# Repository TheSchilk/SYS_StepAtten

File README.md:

# SYS StepAtten

### Philipp Schilk

A 127 Step Relay Step-Attenuator and 4-way input switcher designed to fit into a [Schiit SYS](https://www.schiit.com/products/sys) enclosure.

## Specifications

| **Spec**                 | **Value**                                 |
|--------------------------|-------------------------------------------|
| Inputs                   | 2x Stereo 3.5mm, 2x Stereo RCA            |
| Attenuator Type          | Constant input impedance                  |
| Expected Input Impedance | 10K (can be adjusted)                     |
| Steps                    | 127 + Relay Mute                          |
| Power Input              | 9Vdc, center positive barrel jack. 500mA+ |
| Power Consumption        | Max 2.25W (250mA at 9VDc)                 |
| Control                  | Internal controls or wired remote control |

## Grounding
All inputs are fully isolated from each other.
RCA grounds can be kept seperate or joined. (Internal Jumper)
Audio ground can be kept seperate or joined to digital ground (Internal Jumper)

## Remote Control
Remote Control connector pinout (looking at connector from back of unit):

| 3V    | GND  |
|-------|------|
| **Sense** | **Poti** |

A remote consists of a potentiometer between 3V and GND with wiper connected to 'Poti'
A 10K resistor has to be placed between GND and Sense for the remote to be detected.
If the remote features a switch, it should short Sense to GND.

## Riser Board
Design files for the 3.5mm Connector Riser board [can be found here](https://github.com/TheSchilk/3.5mm_RiserPCB/releases/tag/v0.1).

## Switch Selection

The SYS is normally fitted with a toggle switch (ALPS SPUN191400), but
a momentary version of that switch also exists (ALPS SPUN190900).

The momentary switch is probably the better choice, but just in case
one wants to harvest as many parts as possible from an original SYS,
both are supported by the firmware.

The internal Jumper CFG1 is used to indicate which kind is installed.

|           *Switch*          | *CFG1 Setting* |
|:---------------------------:|:--------------:|
| Momentary (ALPS SPUN190900) |        0       |
|   Toggle (ALPS SPUN191400)  |        1       |

Note that the unit has to be turned off and on again for this setting 
to take effect.

## Schematics, Gerbers, BOMs, ...
See [Github Releases](https://github.com/TheSchilk/SYS_StepAtten/releases).

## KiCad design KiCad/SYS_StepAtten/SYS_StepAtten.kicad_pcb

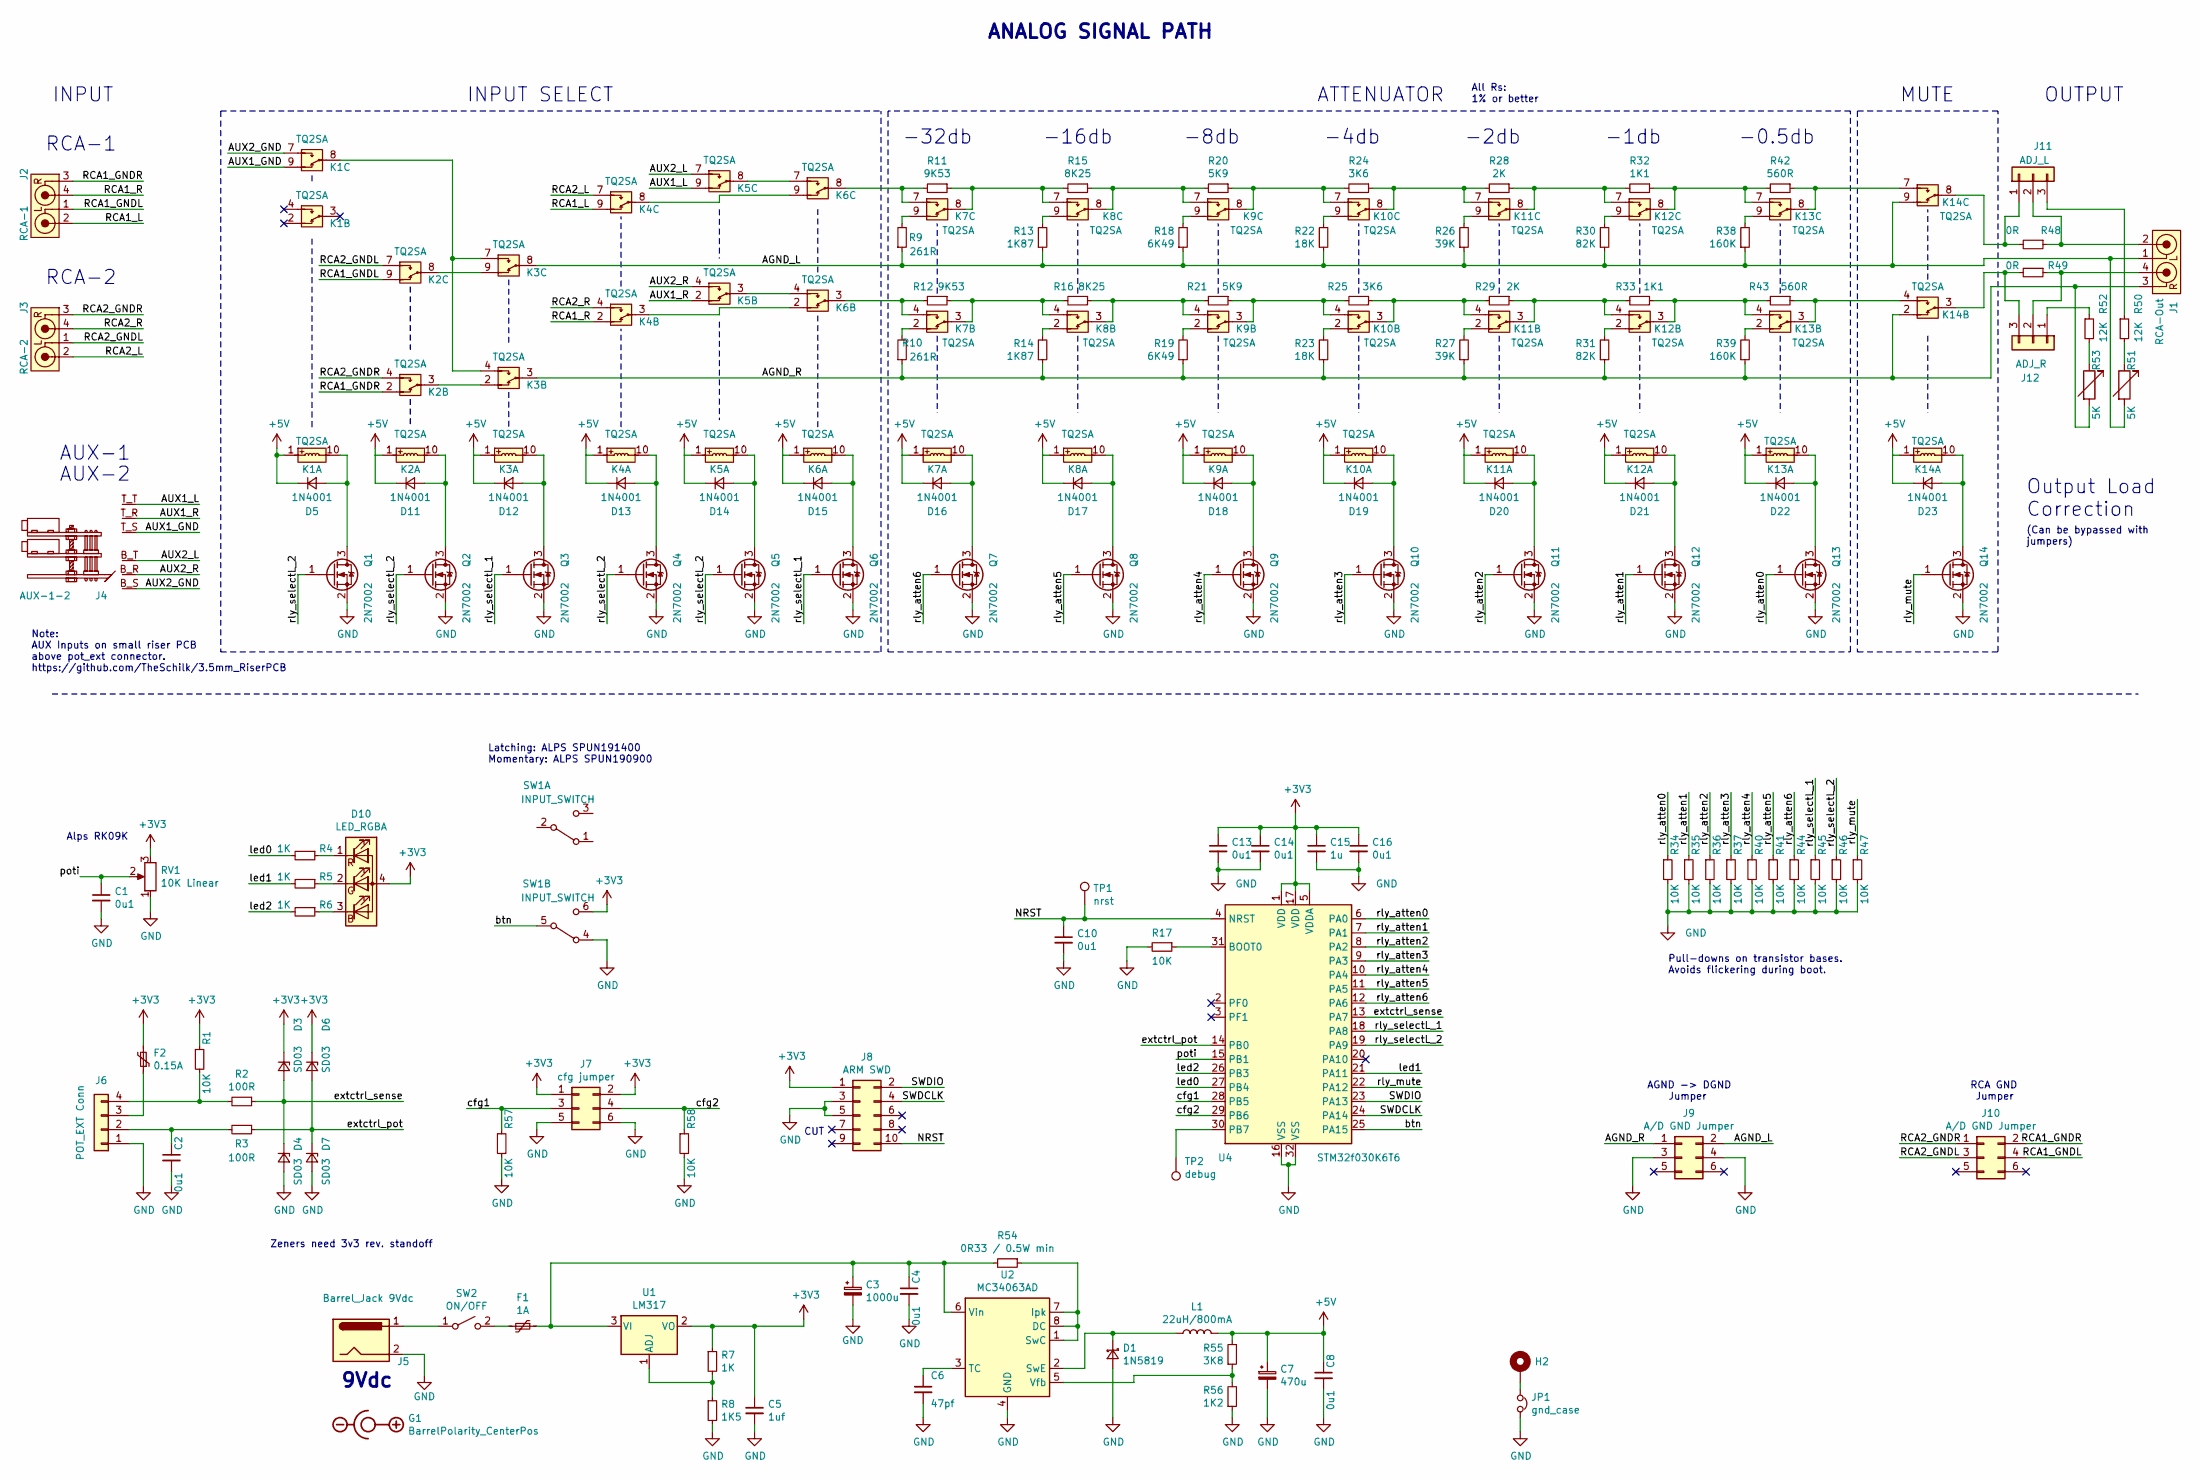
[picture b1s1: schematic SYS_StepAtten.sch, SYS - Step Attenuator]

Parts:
C1, C2, C4, C8, C10, C13, C14, C16: 0u1; C_0603_1608Metric
C3: 1000u; CP_Elec_10x10.5
C5: 1uf; C_0603_1608Metric
C6: 47pf; C_0603_1608Metric
C7: 470u; CP_Elec_8x10.5
C15: 1u; C_0603_1608Metric
D1: 1N5819; D_SOD-123F
D3, D4, D6, D7: SD03; D_SOD-323
D5, D11, D12, D13, D14, D15, D16, D17, D18, D19, D20, D21, D22, D23: 1N4001; D_SOD-123F
D10: LED_RGBA; RGB_LED_1.6x1.6x0.6
F1: 1A; Fuse_1206_3216Metric
F2: 0.15A; Fuse_1206_3216Metric
G1: BarrelPolarity_CenterPos; BarrelPolarity_3mm_CenterPos
H2: MH 1; MountingHole_4.3mm_M4_Pad_Via
J1: RCA-Out; RCA_KobiCon_161-4220-E
J2: RCA-1; RCA_KobiCon_161-4220-E
J3: RCA-2; RCA_KobiCon_161-4220-E
J4: AUX-1-2; 3.5mm_RiserPCB
J5: Barrel_Jack 9Vdc; BarrelJack_Horizontal
J6: POT_EXT Conn; PinHeader_2x02_P2.54mm_Horizontal
J7: cfg jumper; PinHeader_2x03_P2.54mm_Vertical
J8: ARM SWD; PinHeader_2x05_P1.27mm_Vertical_SMD
J9, J10: A/D GND Jumper; PinHeader_2x03_P2.54mm_Vertical
J11: ADJ_L; PinHeader_1x03_P2.54mm_Vertical
J12: ADJ_R; PinHeader_1x03_P2.54mm_Vertical
JP1: gnd_case; R_0603_1608Metric
K1, K2, K3, K4, K5, K6, K7, K8, K9, K10, K11, K12, K13, K14: TQ2SA; Panasonic_TQ2SA
L1: 22uH/800mA; L_Taiyo-Yuden_MD-4040
Q1, Q2, Q3, Q4, Q5, Q6, Q7, Q8, Q9, Q10, Q11, Q12, Q13, Q14: 2N7002; SOT-23
R1, R17, R34, R35, R36, R37, R40, R41, R44, R45, R46, R47, R57, R58: 10K; R_0603_1608Metric
R2, R3: 100R; R_0603_1608Metric
R4, R5, R6, R7: 1K; R_0603_1608Metric
R8: 1K5; R_0603_1608Metric
R9, R10: 261R; R_0603_1608Metric
R11, R12: 9K53; R_0603_1608Metric
R13, R14: 1K87; R_0603_1608Metric
R15, R16: 8K25; R_0603_1608Metric
R18, R19: 6K49; R_0603_1608Metric
R20, R21: 5K9; R_0603_1608Metric
R22, R23: 18K; R_0603_1608Metric
R24, R25: 3K6; R_0603_1608Metric
R26, R27: 39K; R_0603_1608Metric
R28, R29: 2K; R_0603_1608Metric
R30, R31: 82K; R_0603_1608Metric
R32, R33: 1K1; R_0603_1608Metric
R38, R39: 160K; R_0603_1608Metric
R42, R43: 560R; R_0603_1608Metric
R48, R49: 0R; R_0603_1608Metric
R50, R52: 12K; R_0603_1608Metric
R51, R53: 5K; Potentiometer_Bourns_3296W_Vertical
R54: 0R33 / 0.5W min; R_1210_3225Metric
R55: 3K8; R_0603_1608Metric
R56: 1K2; R_0603_1608Metric
RV1: 10K Linear; Potentiometer_Alps_RK09K_Single_Horizontal
SW1: INPUT_SWITCH; ALPS_SPUN191400
SW2: ON/OFF; PinHeader_1x02_P2.54mm_Vertical
TP1: nrst; TestPoint_Pad_2.5x2.5mm
TP2: debug; TestPoint_Pad_2.5x2.5mm
U1: LM317; TO-252-2
U2: MC34063AD; SOIC-8_3.9x4.9mm_P1.27mm
U4: STM32f030K6T6; LQFP-32_7x7mm_P0.8mm

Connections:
+3V3: C5.1, C13.1, C14.1, C15.1, C16.1, D3.1 (K), D6.1 (K), D10.4 (A), F2.2, J7.1, J7.2, J8.1, R1.1, R7.1, RV1.3, SW1.6 (C), U1.2 (VO), U4.1 (VDD), U4.5 (VDDA), U4.17 (VDD)
+5V: C7.1, C8.1, D5.1 (K), D11.1 (K), D12.1 (K), D13.1 (K), D14.1 (K), D15.1 (K), D16.1 (K), D17.1 (K), D18.1 (K), D19.1 (K), D20.1 (K), D21.1 (K), D22.1 (K), D23.1 (K), K1.1, K2.1, K3.1, K4.1, K5.1, K6.1, K7.1, K8.1, K9.1, K10.1, K11.1, K12.1, K13.1, K14.1, L1.2, R55.2
/AGND_L: J1.1, J9.2, K3.8, K14.9, R9.1, R13.1, R18.1, R22.1, R26.1, R30.1, R38.1, R51.2
/AGND_R: J1.3, J9.1, K3.3, K14.2, R10.1, R14.1, R19.1, R23.1, R27.1, R31.1, R39.1, R53.2
/AUX1_GND: J4.T_S, K1.9
/AUX1_L: J4.T_T, K5.9
/AUX1_R: J4.T_R, K5.2
/AUX2_GND: J4.B_S, K1.7
/AUX2_L: J4.B_T, K5.7
/AUX2_R: J4.B_R, K5.4
/NRST: C10.1, J8.10, TP1.1, U4.4 (NRST)
/RCA1_GNDL: J2.1, J10.4, K2.9
/RCA1_GNDR: J2.3, J10.2, K2.2
/RCA1_L: J2.2, K4.9
/RCA1_R: J2.4, K4.2
/RCA2_GNDL: J3.1, J10.3, K2.7
/RCA2_GNDR: J3.3, J10.1, K2.4
/RCA2_L: J3.2, K4.7
/RCA2_R: J3.4, K4.4
/SWDCLK: J8.4, U4.24 (PA14)
/SWDIO: J8.2, U4.23 (PA13)
/btn: SW1.5 (B), U4.25 (PA15)
/cfg1: J7.3, R57.1, U4.28 (PB5)
/cfg2: J7.4, R58.1, U4.29 (PB6)
/extctrl_pot: D6.2 (A), D7.1 (K), R3.1, U4.14 (PB0)
/extctrl_sense: D3.2 (A), D4.1 (K), R2.1, U4.13 (PA7)
/led0: R4.2, U4.27 (PB4)
/led1: R5.2, U4.21 (PA11)
/led2: R6.2, U4.26 (PB3)
/poti: C1.1, RV1.2, U4.15 (PB1)
/rly_atten0: Q13.1 (G), R34.1, U4.6 (PA0)
/rly_atten1: Q12.1 (G), R35.1, U4.7 (PA1)
/rly_atten2: Q11.1 (G), R36.1, U4.8 (PA2)
/rly_atten3: Q10.1 (G), R37.1, U4.9 (PA3)
/rly_atten4: Q9.1 (G), R40.1, U4.10 (PA4)
/rly_atten5: Q8.1 (G), R41.1, U4.11 (PA5)
/rly_atten6: Q7.1 (G), R44.1, U4.12 (PA6)
/rly_mute: Q14.1 (G), R47.1, U4.22 (PA12)
/rly_selectL_1: Q3.1 (G), Q6.1 (G), R45.1, U4.18 (PA8)
/rly_selectL_2: Q1.1 (G), Q2.1 (G), Q4.1 (G), Q5.1 (G), R46.1, U4.19 (PA9)
GND: C1.2, C2.2, C3.2, C4.2, C5.2, C6.2, C7.2, C8.2, C10.2, C13.2, C14.2, C15.2, C16.2, D1.2 (A), D4.2 (A), D7.2 (A), J5.2, J6.1, J7.5, J7.6, J8.3, J8.5, J9.3, J9.4, JP1.2, Q1.2 (S), Q2.2 (S), Q3.2 (S), Q4.2 (S), Q5.2 (S), Q6.2 (S), Q7.2 (S), Q8.2 (S), Q9.2 (S), Q10.2 (S), Q11.2 (S), Q12.2 (S), Q13.2 (S), Q14.2 (S), R8.2, R17.2, R34.2, R35.2, R36.2, R37.2, R40.2, R41.2, R44.2, R45.2, R46.2, R47.2, R56.1, R57.2, R58.2, RV1.1, SW1.4 (A), U2.4 (GND), U4.16 (VSS), U4.32 (VSS)
unnamed: C2.1, J6.2, R3.2
unnamed: C3.1, C4.1, F1.1, R54.2, U1.3 (VI), U2.6 (Vin)
unnamed: C6.1, U2.3 (TC)
unnamed: D1.1 (K), L1.1, U2.2 (SwE)
unnamed: D5.2 (A), K1.10, Q1.3 (D)
unnamed: D10.1 (RK), R4.1
unnamed: D10.2 (GK), R5.1
unnamed: D10.3 (BK), R6.1
unnamed: D11.2 (A), K2.10, Q2.3 (D)
unnamed: D12.2 (A), K3.10, Q3.3 (D)
unnamed: D13.2 (A), K4.10, Q4.3 (D)
unnamed: D14.2 (A), K5.10, Q5.3 (D)
unnamed: D15.2 (A), K6.10, Q6.3 (D)
unnamed: D16.2 (A), K7.10, Q7.3 (D)
unnamed: D17.2 (A), K8.10, Q8.3 (D)
unnamed: D18.2 (A), K9.10, Q9.3 (D)
unnamed: D19.2 (A), K10.10, Q10.3 (D)
unnamed: D20.2 (A), K11.10, Q11.3 (D)
unnamed: D21.2 (A), K12.10, Q12.3 (D)
unnamed: D22.2 (A), K13.10, Q13.3 (D)
unnamed: D23.2 (A), K14.10, Q14.3 (D)
unnamed: F1.2, SW2.2 (B)
unnamed: F2.1, J6.3
unnamed: H2.1, JP1.1
unnamed: J1.2, J11.2, R48.1
unnamed: J1.4, J12.2, R49.1
unnamed: J5.1, SW2.1 (A)
unnamed: J6.4, R1.2, R2.2
unnamed: J11.1, K14.8, R48.2
unnamed: J11.3, R50.1
unnamed: J12.1, R52.1
unnamed: J12.3, K14.3, R49.2
unnamed: K1.8, K3.4, K3.7
unnamed: K2.3, K3.2
unnamed: K2.8, K3.9
unnamed: K4.3, K6.2
unnamed: K4.8, K6.9
unnamed: K5.3, K6.4
unnamed: K5.8, K6.7
unnamed: K6.3, K7.4, R12.2
unnamed: K6.8, K7.7, R11.2
unnamed: K7.2, R10.2
unnamed: K7.3, K8.4, R12.1, R16.2
unnamed: K7.8, K8.7, R11.1, R15.2
unnamed: K7.9, R9.2
unnamed: K8.2, R14.2
unnamed: K8.3, K9.4, R16.1, R21.2
unnamed: K8.8, K9.7, R15.1, R20.2
unnamed: K8.9, R13.2
unnamed: K9.2, R19.2
unnamed: K9.9, R18.2
unnamed: K10.2, R23.2
unnamed: K10.3, K11.4, R25.1, R29.2
unnamed: K9.3, K10.4, R21.1, R25.2
unnamed: K9.8, K10.7, R20.1, R24.2
unnamed: K10.8, K11.7, R24.1, R28.2
unnamed: K10.9, R22.2
unnamed: K11.2, R27.2
unnamed: K11.3, K12.4, R29.1, R33.2
unnamed: K11.8, K12.7, R28.1, R32.2
unnamed: K11.9, R26.2
unnamed: K12.2, R31.2
unnamed: K12.3, K13.4, R33.1, R43.2
unnamed: K12.8, K13.7, R32.1, R42.2
unnamed: K12.9, R30.2
unnamed: K13.2, R39.2
unnamed: K13.3, K14.4, R43.1
unnamed: K13.8, K14.7, R42.1
unnamed: K13.9, R38.2
unnamed: R7.2, R8.1, U1.1 (ADJ)
unnamed: R17.1, U4.31 (BOOT0)
unnamed: R50.2, R51.1
unnamed: R52.2, R53.1
unnamed: R54.1, U2.1 (SwC), U2.7 (Ipk), U2.8 (DC)
unnamed: R55.1, R56.2, U2.5 (Vfb)
unnamed: TP2.1, U4.30 (PB7)

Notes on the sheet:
ATTENUATOR
INPUT SELECT
ANALOG SIGNAL PATH
OUTPUT
INPUT
CUT
MUTE
AUX-2
AUX-1
RCA-2
RCA-1
-0.5db
-1db
-2db
-4db
-8db
-16db
-32db
Output Load Correction
All Rs: 1% or better
9Vdc
Note: AUX Inputs on small riser PCB above pot_ext connector. https://github.com/TheSchilk/3.5mm_RiserPCB
AGND -> DGND Jumper
RCA GND Jumper
Zeners need 3v3 rev. standoff
Pull-downs on transistor bases. Avoids flickering during boot.
Latching: ALPS SPUN191400 Momentary: ALPS SPUN190900
Alps RK09K
(Can be bypassed with jumpers)

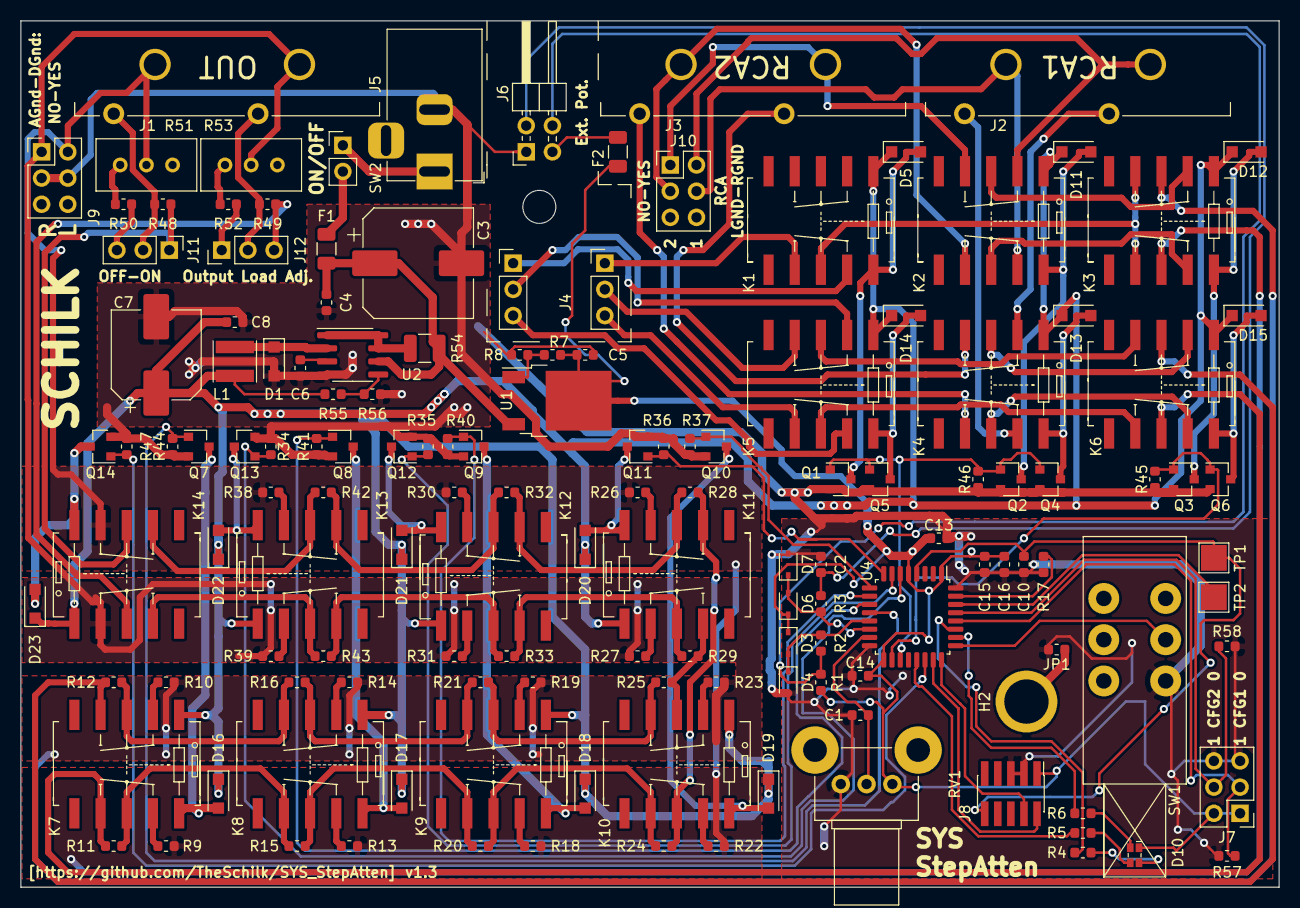
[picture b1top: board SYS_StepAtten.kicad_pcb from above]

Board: 2 copper layers, 122.0 x 84.0 mm, 145 parts (1 on the bottom side), 117 nets.

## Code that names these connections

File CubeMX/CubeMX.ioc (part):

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Mcu.Name=STM32F030K6Tx
Mcu.Package=LQFP32
Mcu.UserName=STM32F030K6Tx
PA0.GPIOParameters=GPIO_Label
PA0.GPIO_Label=atten0
PA0.Signal=GPIO_Output
PA1.GPIOParameters=GPIO_Label
PA1.GPIO_Label=atten1
PA1.Signal=GPIO_Output
PA11.GPIOParameters=GPIO_Label
PA11.GPIO_Label=led1
PA11.Signal=GPIO_Output
PA12.GPIOParameters=GPIO_Label
PA12.GPIO_Label=mute
PA12.Signal=GPIO_Output
PA13.Mode=Serial_Wire
PA13.Signal=SYS_SWDIO
PA14.Mode=Serial_Wire
PA14.Signal=SYS_SWCLK
PA15.GPIOParameters=GPIO_Label
PA15.GPIO_Label=btn
PA15.Signal=GPIO_Input
PA2.GPIOParameters=GPIO_Label
PA2.GPIO_Label=atten2
PA2.Signal=GPIO_Output
PA3.GPIOParameters=GPIO_Label
PA3.GPIO_Label=atten3
PA3.Signal=GPIO_Output
PA4.GPIOParameters=GPIO_Label
PA4.GPIO_Label=atten4
PA4.Signal=GPIO_Output
PA5.GPIOParameters=GPIO_Label
PA5.GPIO_Label=atten5
PA5.Signal=GPIO_Output
PA6.GPIOParameters=GPIO_Label
PA6.GPIO_Label=atten6
PA6.Signal=GPIO_Output
PA7.GPIOParameters=GPIO_Label
PA7.GPIO_Label=extctrl_sense
PA7.Mode=IN7
PA7.Signal=ADC_IN7
PA8.GPIOParameters=GPIO_Label
PA8.GPIO_Label=select1
PA8.Signal=GPIO_Output
PA9.GPIOParameters=GPIO_Label
PA9.GPIO_Label=select2
PA9.Signal=GPIO_Output
PB0.GPIOParameters=GPIO_Label
PB0.GPIO_Label=extctrl_pot
PB0.Mode=IN8
PB0.Signal=ADC_IN8
PB1.GPIOParameters=GPIO_Label
PB1.GPIO_Label=pot_in
PB1.Mode=IN9
PB1.Signal=ADC_IN9
PB3.GPIOParameters=GPIO_Label
PB3.GPIO_Label=led2
PB3.Signal=GPIO_Output
PB4.GPIOParameters=GPIO_Label
PB4.GPIO_Label=led0
PB4.Signal=GPIO_Output
PB5.GPIOParameters=GPIO_Label
PB5.GPIO_Label=config1
PB5.Signal=GPIO_Input
PB6.GPIOParameters=GPIO_Label
PB6.GPIO_Label=config2
PB6.Signal=GPIO_Input
PB7.GPIOParameters=GPIO_Label
PB7.GPIO_Label=DBG_TP
PB7.Signal=GPIO_Output
PF0-OSC_IN.Mode=HSE-External-Oscillator
PF0-OSC_IN.Signal=RCC_OSC_IN
PF1-OSC_OUT.Mode=HSE-External-Oscillator
PF1-OSC_OUT.Signal=RCC_OSC_OUT
board=custom

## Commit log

2020-03-10 Setup KiCad Project, added Relay Symbol
2020-03-15 Added Multi-Device Symbol
2020-03-16 Added Draft of Analog Signal Path
2020-03-21 Signal path layout done, no resistor values yet
    sync
    Analog path layout done, no resistor vals yet
2020-04-07 fixed labels
2020-04-07 Schematic first draft
    Finished Schematic
2020-04-07 Updated Riser board footprint
2020-04-07 Schematic Refinments, Changed Relays and moved to own power rail
2020-04-08 Basic Sorting Done
2020-04-08 Setup netclasses
2020-04-08 finished testing board v0.0
2020-04-08 pulled in fixed footprint for alps switch
2020-04-08 moved silkscreen lbl
2020-04-08 Added page info, exported gerber+schm. ready for production
2020-04-23 Added CubeMX file
2020-04-23 Moved Around .gitignores, added gitignore for firmware
2020-04-23 Added Debug Pin to CubeMX Setup
2020-05-04 Pulled in new Switch footprint
2020-05-17 Deleted Old PCB, will have to redo
2020-05-17 Fixed Output RCA Jack connection
2020-05-17 Cleared Annotations, Will have to redo pcb anyway
2020-05-23 Added Series Output Load Adjustment
2020-05-23 Reassigned Selection Relays
2020-05-23 Changed Mute to be short
2020-05-23 Added Pulldowns on transitors
2020-05-23 Added Ground Config Jumpers
2020-05-23 Changed Mounting Hole Grounding
2020-05-24 Updated Power Supply
2020-05-24 Pulled in v0.1 3.5mm Riser PCB
2020-05-24 Changed to RGB LED
2020-05-24 Pulled in new RCA_Stereo Symbol, Made sure L/R Channels are correct
2020-05-24 Added ESD protection to external poti interface
2020-05-24 Added Mounting Hole Footprint
2020-05-24 Annotated Schematic, Added last few footprints
2020-05-24 SYS Base Layout
2020-05-24 Pulled in 3.5mm Riser again to fix problem with hole spacing...
2020-05-25 Layout1
2020-05-25 Base without relays
2020-05-25 Vertical
2020-05-25 No 2nd Mounting Hole
2020-05-25 1st Draft Parts Placement
2020-05-26 Half finished
2020-05-27 First Routing Draft
2020-06-04 Generated production files for v1.0
2020-06-04 Small Fixes. Pfuh.
2020-06-04 Regenerated Production Files
2020-07-09 Removed FPU warning
2020-07-09 Empty STM32CubeIDE Project
2020-07-09 Added ST STDPeriphLib Version 1.5.0 (STSW-STM32048)
2020-07-09 Simple Test ADC-> Atten
2020-07-09 Added ARM/ST CMSIS Version 1.5.0 (STSW-STM32048)
2020-07-09 Basic Functionally implemented
2020-07-09 Updated firmware for new pinout
2020-07-11 Updated UI, removed external control for now
2020-07-11 Cleanup
2020-07-12 Updated Schematic
    - Changed to DC Input
    - Changed to Switchmode powersupply
    - Updated external interface to support button
    - Added jumper for load-adjustement
2020-07-12 Layout updated
2020-07-12 Updated PCB
2020-07-12 Generated Production Files
2020-07-12 Added changelog
2020-07-12 First draft README
2020-08-28 PCB v1.1 ready.
2020-08-28 Added Power Specs.
2020-08-29 Added all 3 UI modes.
2020-08-29 Added Pulldowns to configuration jumpers
2020-08-29 Generated production files.
2020-08-29 Typo
2020-08-30 Basic Flash input-setting retention working.
2020-08-30 Slight refactor + Some Documentation
2020-08-30 Disable interrupts during Flash operations
2020-08-30 Flash code should be done.
2020-08-30 Removed 'Select' UI mode and 'UI Mode' paradigm
2020-08-30 Groundwork for external control
2020-08-30 Fixed pinout
2020-08-30 Updated to pinout v1.3
2020-08-30 Mute on powerup.
2020-08-30 Implemented external control.
2020-08-30 Added ADC scaling to utilise whole atten range
2020-08-30 Added fuse to ext. ctrl. connection
2020-08-30 Updated Layout.
2020-08-30 Generated v1.3 Production Files
2020-08-30 Updated changelod.md for pcb_v1.3
2020-08-30 Basic Documentation Updates
2020-08-30 Cleanup and refactor
2020-09-27 Flash LED on when input is saved.
2020-09-27 Mute when potentiometer at 0
2020-10-31 Hide BOM from language Github's Language Stats
2020-10-31 Added License
2020-10-31 Small README updates
2020-10-31 Added better Render
2020-10-31 Image Resize
2021-05-24 Clean up github language stats
2021-05-27 Added better pictures
